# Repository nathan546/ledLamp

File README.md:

## Synopsis

Work in progress.  This is for an LED lamp I'm currently developing.

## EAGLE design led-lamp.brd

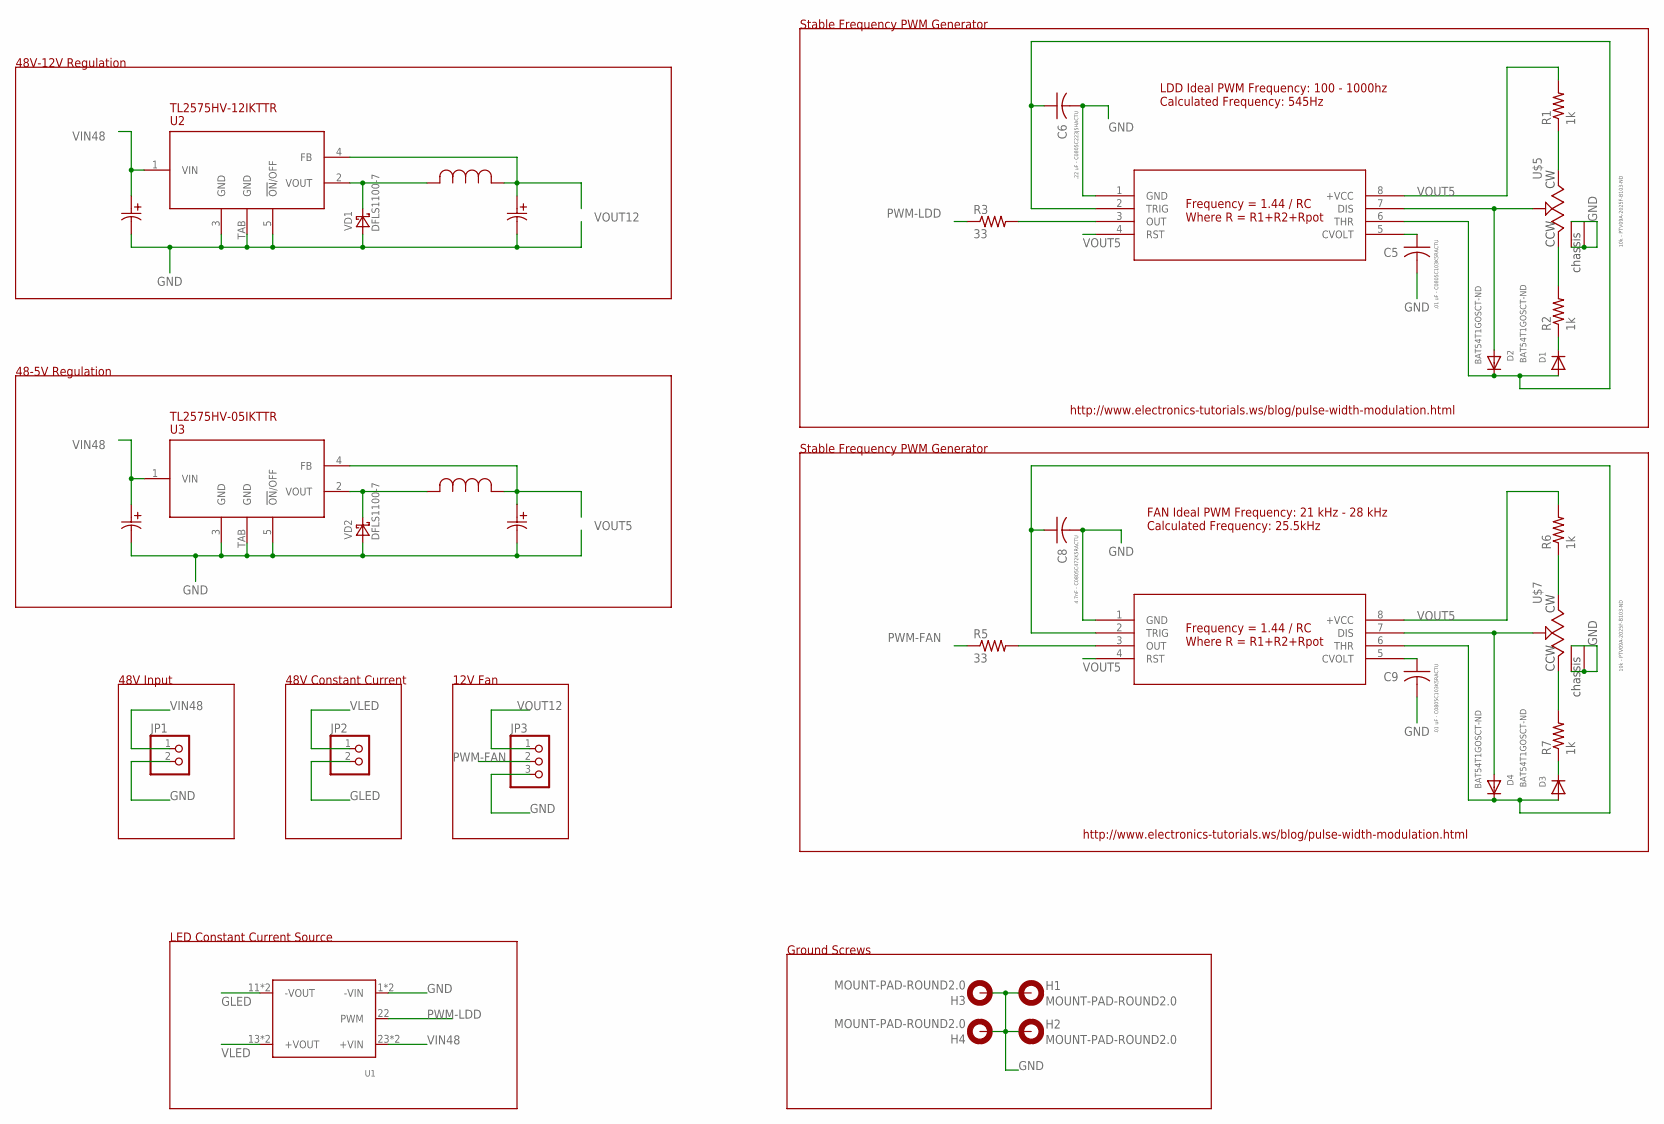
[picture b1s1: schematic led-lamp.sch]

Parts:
C1, C3: UVR1H101MPD; PCAP_8X11_5-THRU-ELECT
C2, C4: UVR1C331MPD; PCAP_8X11_5-THRU-ELECT
C5, C9: .01 uF - C0805C103K5RACTU; C0805K
C6: .22 uF - C0805C223J5HACTU; C0805K
C8: 4.7nF - C0805C472K5RACTU; C0805K
D1, D2, D3, D4: BAT54T1GOSCT-ND; SOD-123
H1, H2, H3, H4: MOUNT-PAD-ROUND2.0; 2,0-PAD
JP1, JP2: PINHD-1X2; 1X02
JP3: PINHD-1X3; 1X03
L1, L2: SRN1060-331M; IND_BOURNS_SRN1060
R1, R2, R6, R7: 1k; R0805
R3, R5: 33; R0805
U1: LDD-H
U2: TL2575HV-12IKTTR; TO-263-5
U3: TL2575HV-05IKTTR; TO-263-5
U4, U6: LM555CMX; M08A
U$5, U$7: 10k - PTV09A-2025F-B103-ND; PTV09A-2
VD1, VD2: DFLS1100-7; POWER-DI-123

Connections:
GLED: JP2.2, U1.11 (-VOUT), U1.12 (-VOUT)
GND: C1.2 (22), C2.2 (22), C3.2 (22), C4.2 (22), C5.2, C6.2, C8.2, C9.2, H1.B2,8, H2.B2,8, H3.B2,8, H4.B2,8, JP1.2, JP3.3, U1.1 (-VIN), U1.2 (-VIN), U2.3 (GND), U2.5 (!ON!/OFF), U2.TAB (GND), U3.3 (GND), U3.5 (!ON!/OFF), U3.TAB (GND), U4.1 (GND), U6.1 (GND), U$5.4 (CHASSIS1), U$5.5 (CHASSIS), U$7.4 (CHASSIS1), U$7.5 (CHASSIS), VD1.A, VD2.A
unnamed: L1.2, U2.2 (VOUT), VD1.C
unnamed: L2.2, U3.2 (VOUT), VD2.C
unnamed: D2.A, U4.7 (DIS), U$5.2 (WIPER)
unnamed: R2.2, U$5.1 (CCW)
unnamed: R1.1, U$5.3 (CW)
unnamed: D1.C, R2.1
unnamed: R3.2, U4.3 (OUT)
unnamed: C5.1, U4.5 (CVOLT)
unnamed: C6.1, D1.A, D2.C, U4.2 (TRIG), U4.6 (THR)
unnamed: R5.2, U6.3 (OUT)
unnamed: C8.1, D3.A, D4.C, U6.2 (TRIG), U6.6 (THR)
unnamed: D4.A, U6.7 (DIS), U$7.2 (WIPER)
unnamed: R7.2, U$7.1 (CCW)
unnamed: R6.1, U$7.3 (CW)
unnamed: D3.C, R7.1
unnamed: C9.1, U6.5 (CVOLT)
PWM-FAN: JP3.2, R5.1
PWM-LDD: R3.1, U1.22 (PWM)
VIN48: C1.1 (11), C3.1 (11), JP1.1, U1.23 (+VIN), U1.24 (+VIN), U2.1 (VIN), U3.1 (VIN)
VLED: JP2.1, U1.13 (+VOUT), U1.14 (+VOUT)
VOUT5: C4.1 (11), L2.1, R1.2, R6.2, U3.4 (FB), U4.4 (RST), U4.8 (+VCC), U6.4 (RST), U6.8 (+VCC)
VOUT12: C2.1 (11), JP3.1, L1.1, U2.4 (FB)

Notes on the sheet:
48V-12V Regulation
48-5V Regulation
Frequency = 1.44 / RC Where R = R1+R2+Rpot
LDD Ideal PWM Frequency: 100 - 1000hz Calculated Frequency: 545Hz
Stable Frequency PWM Generator
FAN Ideal PWM Frequency: 21 kHz - 28 kHz Calculated Frequency: 25.5kHz
http://www.electronics-tutorials.ws/blog/pulse-width-modulation.html
48V Input
LED Constant Current Source
48V Constant Current
Ground Screws
12V Fan

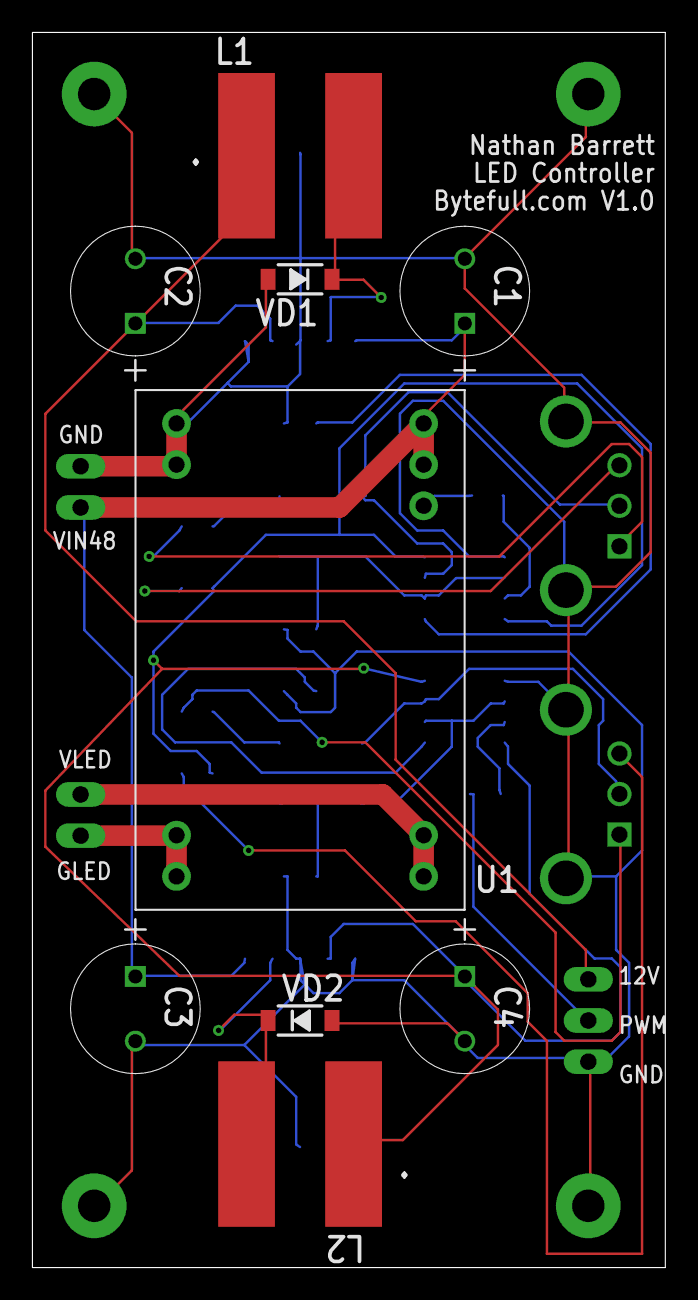
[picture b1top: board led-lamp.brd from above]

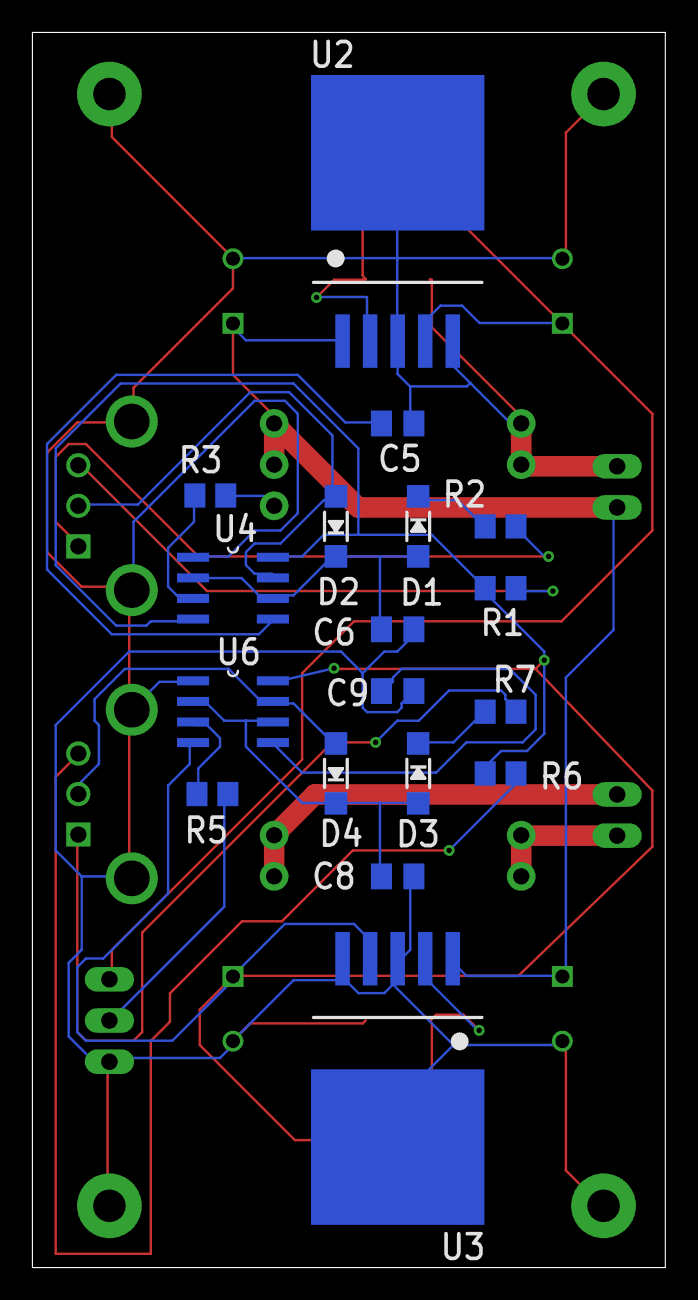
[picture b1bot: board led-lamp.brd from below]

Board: 2 copper layers, 39.0 x 76.2 mm, 36 parts (18 on the bottom side), 24 nets.

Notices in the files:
parts and their libraries:
COPYRIGHT: Copyright (C) 2015 Accelerated Designs. All rights reserved
